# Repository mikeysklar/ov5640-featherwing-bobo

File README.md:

# OV5640 FeatherWing BoBo  

FeatherWing PCB that connects to the OV5640 camera breakout module from Adafruit 

---

## Overview

- OV5640 camera breakout supports both header configurations
- Converts the OV5640 Breakout to a FeatherWing format
- Leaves SPI pins available for SD / SDIO use
- Third header row for breadboard-friendly layouts
- Single Sided PCB for easy rapid prototyping at home
- Compatible with **most Feather boards**
- Tested with **Feather ESP32-S3**

---

## BOM

| Item | Description |
|---|---|
| [Adafruit ESP32-S3 Feather with 4MB Flash 2MB PSRAM – STEMMA QT / Qwiic](https://www.adafruit.com/product/5477) | ESP32-S3 Feather board with 4 MB Flash, 2 MB PSRAM |
| [Adafruit OV5640 Camera Breakout – 120 Degree Lens with Autofocus](https://www.adafruit.com/product/5838) | OV5640 camera module, 120° lens, autofocus |
| [FeatherWing Doubler – Prototyping Add-on For All Feather Boards](https://www.adafruit.com/product/2890) | FeatherWing prototyping add-on board |
| [Single-row SMT headers](https://www.aliexpress.us/item/3256805008610566.html) | Surface-mount single-row pin headers |
| [Double-row SMT headers](https://www.aliexpress.us/item/3256803267239198.html) | Surface-mount double-row pin headers |

---

## Backstory

**OV5640 FeatherWing BoBo** was created to solve a real-world wiring problem discussed 
on the forums [Adafruit forums](https://forums.adafruit.com/viewtopic.php?t=221951).

Special thanks to [Jerry Needell for his reference design and example code](https://github.com/jerryneedell/mycamera). 

---

## CircuitPython

- Tested on v10.0.3
- required libraries:
  - @jerryn [mycamera](https://github.com/jerryneedell/mycamera/tree/main) 
  - adafruit_requests 
  - adafruit_io

---

## Etching Settings

---

## Stencil

---

## Schematic

---

## PCB

---

## KiCAD 3D

---

## Snapshot Test Code

---

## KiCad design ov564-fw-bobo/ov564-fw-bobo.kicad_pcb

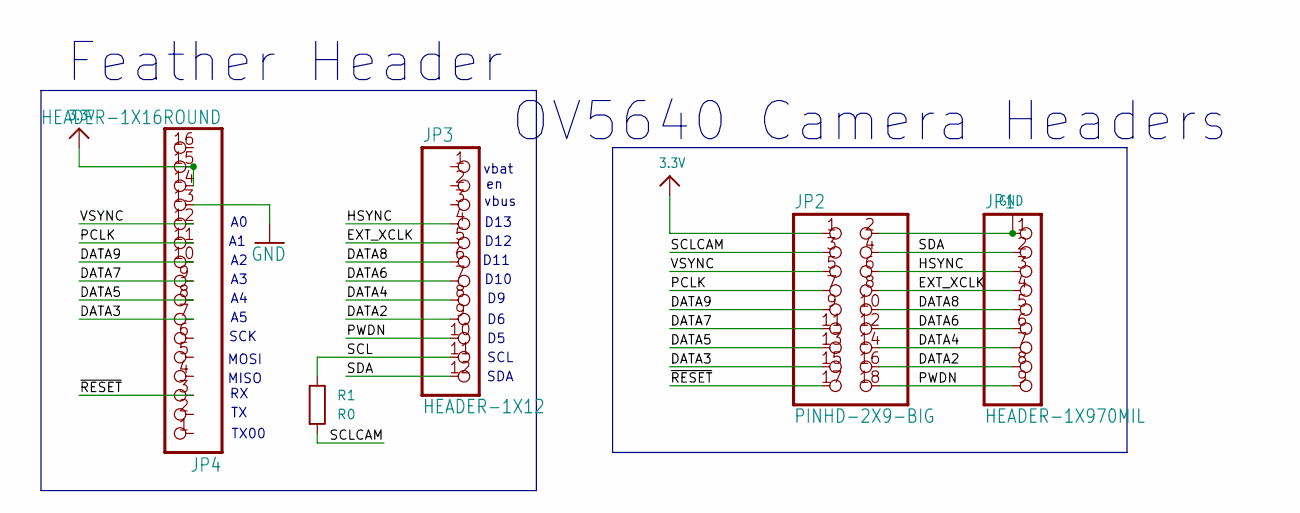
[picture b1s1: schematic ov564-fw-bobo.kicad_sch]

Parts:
JP1: HEADER-1X970MIL; PinHeader_1x09_P2.54mm_Vertical_SMD_Pin1Left
JP2: PINHD-2X9-BIG; PinHeader_2x09_P2.54mm_Vertical_SMD
JP3: HEADER-1X12; PinSocket_1x12_P2.54mm_Vertical
JP4: HEADER-1X16ROUND; PinHeader_1x16_P2.54mm_Vertical
R1: R0; R_0805_2012Metric

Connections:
3.3V: JP2.1, JP4.14, JP4.15
/DATA2: JP1.8, JP2.16, JP3.9
/DATA3: JP2.15, JP4.7
/DATA4: JP1.7, JP2.14, JP3.8
/DATA5: JP2.13, JP4.8
/DATA6: JP1.6, JP2.12, JP3.7
/DATA7: JP2.11, JP4.9
/DATA8: JP1.5, JP2.10, JP3.6
/DATA9: JP2.9, JP4.10
/EXT_XCLK: JP1.4, JP2.8, JP3.5
/HSYNC: JP1.3, JP2.6, JP3.4
/PCLK: JP2.7, JP4.11
/PWDN: JP1.9, JP2.18, JP3.10
/SCL: JP3.11, R1.1
/SCLCAM: JP2.3, R1.2
/SDA: JP1.2, JP2.4, JP3.12
/VSYNC: JP2.5, JP4.12
/~RESET: JP2.17, JP4.3
GND: JP1.1, JP2.2, JP4.13

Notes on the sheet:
D12
D11
MISO
SCL
vbus
D13
MOSI
D10
SCK
Feather Header
TX00
SDA
OV5640 Camera Headers
vbat

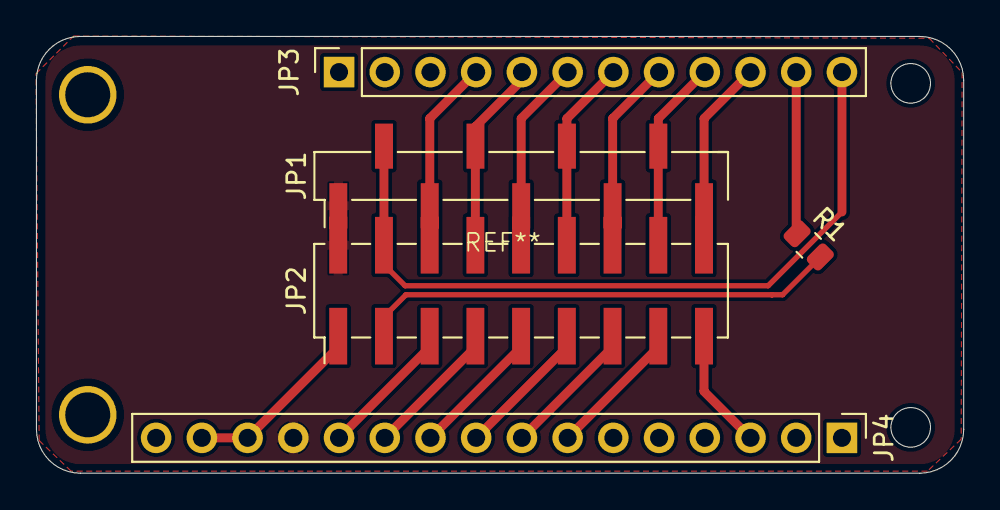
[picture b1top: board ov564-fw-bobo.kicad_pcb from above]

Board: 2 copper layers, 51.5 x 24.3 mm, 5 parts (0 on the bottom side), 19 nets.

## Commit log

2026-01-10 init sch done
2026-01-12 routed
2026-01-13 increased FW size, added resistor jump
2026-01-22 readme
2026-01-22 readme reformat
2026-01-22 bom addded
2026-01-23 format README
2026-01-31 images / jerryn code
2026-01-31 working with AIO
